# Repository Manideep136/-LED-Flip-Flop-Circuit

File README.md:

# -LED-Flip-Flop-Circuit

# LED Flip-Flop Circuit PCB

## 📌 Project Overview

This project is a **LED Flip-Flop Circuit PCB** designed using **KiCad**.

The circuit alternately switches between two LEDs, creating a simple blinking/flip-flop effect. The PCB was designed to provide a compact and organized implementation of the circuit using standard electronic components.

The project focuses on the complete PCB design process, including schematic creation, footprint assignment, component placement, PCB routing, and Design Rules Check (DRC).

---

## 🎯 Project Objectives

- Design a simple LED flip-flop circuit.
- Create the schematic in KiCad.
- Assign suitable footprints to all components.
- Design a compact PCB layout.
- Route all electrical connections properly.
- Add PCB labels and component references.
- Perform ERC/DRC checks before fabrication.
- Generate manufacturing files when required.

---

## ⚙️ Working Principle

The LED flip-flop circuit uses a transistor-based switching arrangement to alternately turn two LEDs ON and OFF.

When one transistor conducts, one LED is activated while the other remains OFF. The circuit then changes state, causing the LEDs to switch alternately.

### Basic operation

``
        +VCC
         │
      ┌──┴──┐
      │     │
     LED1  LED2
      │     │
     Q1     Q2
      │     │
      └──┬──┘
         │
        GND

   Q1 and Q2 alternately switch ON/OFF

🧩 PCB Design Process
1. Schematic Design

The circuit schematic was created in KiCad with all components and electrical connections.

2. Footprint Assignment

Suitable PCB footprints were assigned to each component based on the physical component/package being used.

3. PCB Layout

The schematic was transferred to the PCB Editor and the components were arranged to create a compact and organized board.

4. Routing

Copper tracks were routed between the components according to the schematic connections.

5. Design Rules Check

The PCB was checked using KiCad's Design Rules Check (DRC) to identify issues such as:

Clearance violations
Unconnected nets
Track width violations
Pad clearance problems
Board-edge clearance problems
6. Final Verification

The PCB layout was visually inspected and checked before preparing the manufacturing files.

📐 PCB Features
Compact PCB layout
Two alternating LEDs
Through-hole/component footprints where applicable
Clearly marked component references
Dedicated power input
Organized component placement
KiCad DRC verification
Suitable for PCB fabrication

🚀 Future Improvements

Possible improvements include:

Add a power indicator LED
Add adjustable blinking speed
Use a potentiometer for frequency control
Improve PCB size and component placement
Add mounting holes
Add polarity and power markings
Manufacture and test the PCB
Create an SMD version of the circuit
📚 Learning Outcomes

Through this project, the following PCB design skills were practiced:

KiCad schematic design
Component and footprint selection
PCB component placement
Through-hole PCB design
Copper track routing
PCB layout optimization
ERC and DRC checking
Gerber generation
PCB documentation
🛠️ Tools & Technologies

Design Software: KiCad
PCB Design: KiCad PCB Editor
Schematic: KiCad Schematic Editor
Verification: ERC / DRC
Output: Gerber + Drill Files

 Project

LED Flip-Flop Circuit PCB

Designed as a practical electronics PCB design project using KiCad.

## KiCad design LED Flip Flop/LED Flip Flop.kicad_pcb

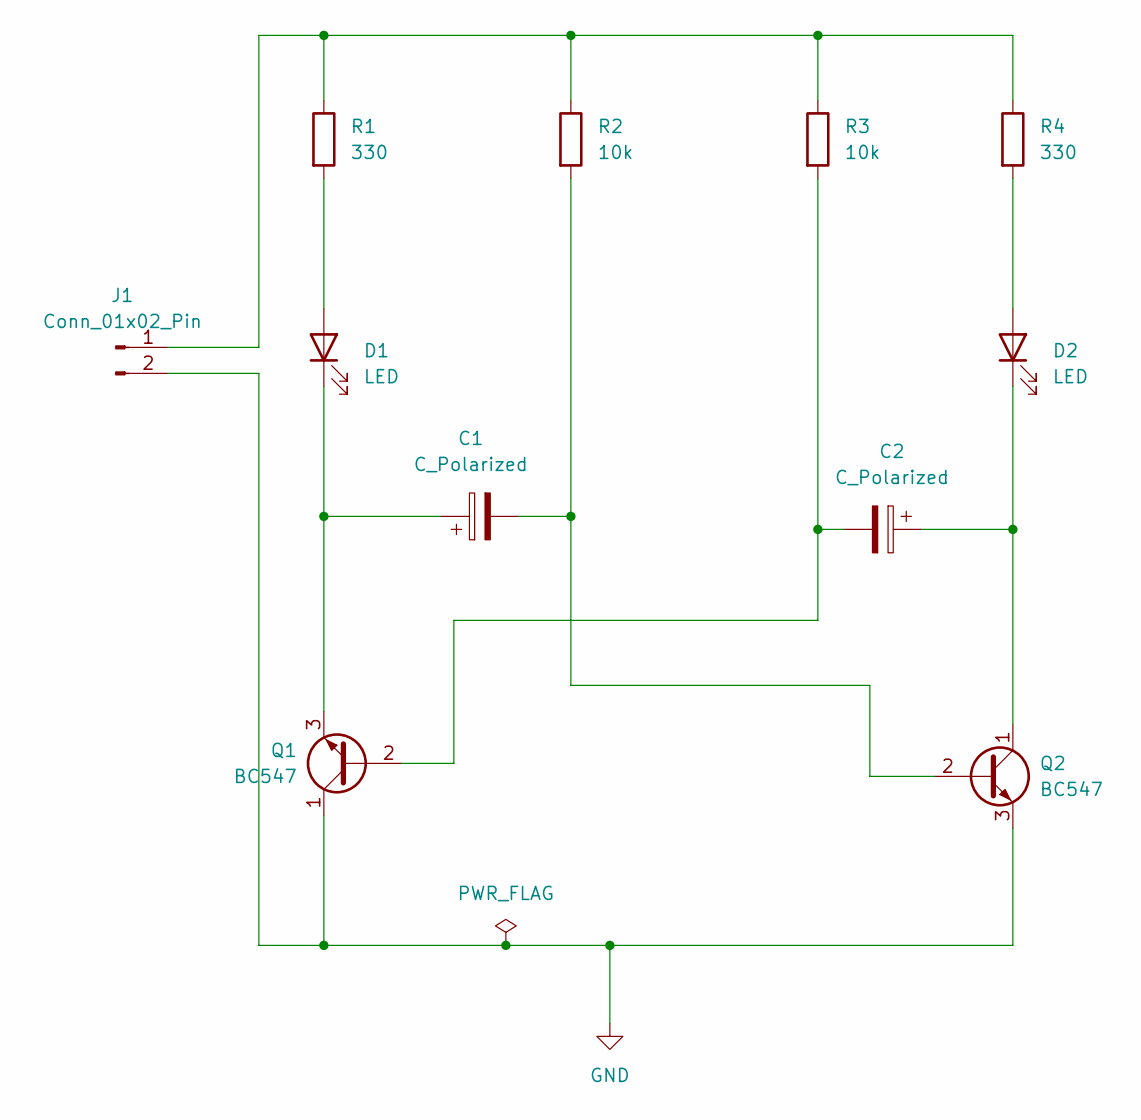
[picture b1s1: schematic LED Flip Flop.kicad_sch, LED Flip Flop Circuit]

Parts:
C1, C2: C_Polarized; CP_Radial_D6.3mm_P2.50mm
D1, D2: LED; LED_D5.0mm
J1: Conn_01x02_Pin; PinHeader_1x02_P2.54mm_Vertical
Q1, Q2: BC547; TO-92_Inline
R1, R4: 330; R_Axial_DIN0204_L3.6mm_D1.6mm_P5.08mm_Horizontal
R2, R3: 10k; R_Axial_DIN0204_L3.6mm_D1.6mm_P5.08mm_Horizontal

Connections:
GND: J1.2, Q1.1 (C), Q2.3 (E)
unnamed: D1.2 (A), R1.2
unnamed: C1.1, D1.1 (K), Q1.3 (E)
unnamed: D2.2 (A), R4.2
unnamed: C2.1, D2.1 (K), Q2.1 (C)
unnamed: J1.1, R1.1, R2.1, R3.1, R4.1
unnamed: C2.2, Q1.2 (B), R3.2
unnamed: C1.2, Q2.2 (B), R2.2

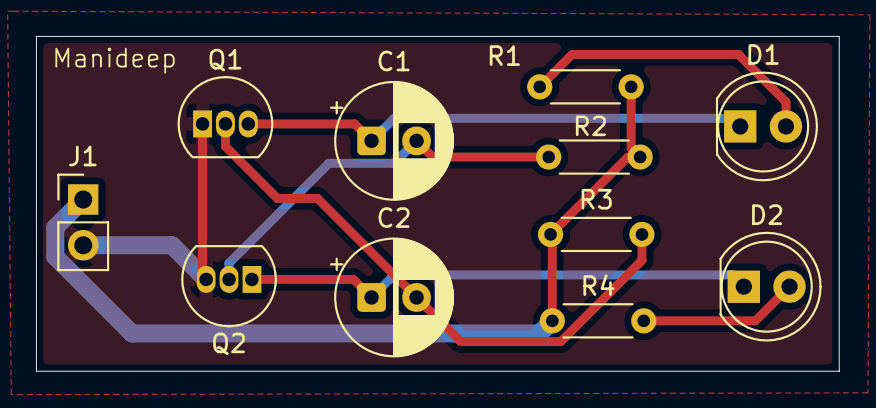
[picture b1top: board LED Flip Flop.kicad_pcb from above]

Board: 2 copper layers, 44.6 x 18.6 mm, 11 parts (0 on the bottom side), 8 nets.
